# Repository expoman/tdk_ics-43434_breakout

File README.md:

# tdk_ics-43434_breakout
small breakout board for the TDK ICS-43434 microphone chip

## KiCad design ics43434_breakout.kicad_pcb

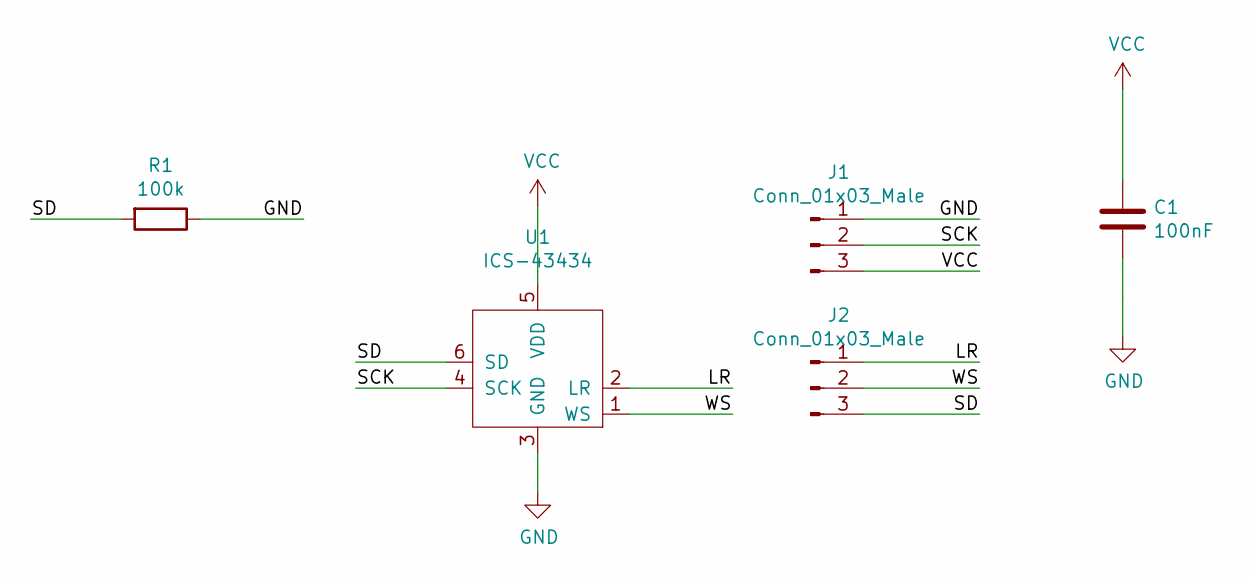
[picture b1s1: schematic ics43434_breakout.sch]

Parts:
C1: 100nF; C_0603_1608Metric_Pad1.05x0.95mm_HandSolder
J1, J2: Conn_01x03_Male; PinSocket_1x03_P2.54mm_Vertical
R1: 100k; R_0603_1608Metric_Pad1.05x0.95mm_HandSolder
U1: ICS-43434; TDK_ICS-43434

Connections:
/LR: J2.1, U1.2 (LR)
/SCK: J1.2, U1.4 (SCK)
/SD: J2.3, R1.2, U1.6 (SD)
/WS: J2.2, U1.1 (WS)
GND: C1.2, J1.1, R1.1, U1.3 (GND)
VCC: C1.1, J1.3, U1.5 (VDD)

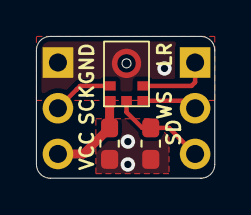
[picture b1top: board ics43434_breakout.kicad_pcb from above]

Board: 2 copper layers, 9.9 x 7.9 mm, 5 parts (0 on the bottom side), 6 nets.

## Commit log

2020-01-23 add project/schematic/board files
    - components placed
    - lines and planes drawn
2020-01-23 update pcb
    - add silkscreen pin functions
2020-01-23 add SD pull-down resistor
2020-01-24 remove 10uF capacitor
    adapt layout
2020-01-24 squeeze layout to 9.91x7.87mm
2020-01-24 move silkscreen text
2020-01-24 fix gnd plane on bottom
2020-02-03 made corners of the board round
